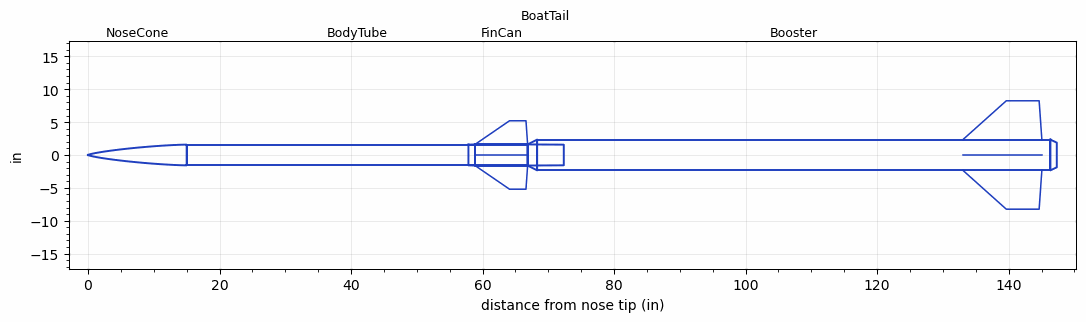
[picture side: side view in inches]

<RASAeroDocument>
 <FileVersion>2</FileVersion>
 <RocketDesign>
  <NoseCone>
   <Length>15</Length>
   <Diameter>3.15</Diameter>
   <Shape>Von Karman Ogive</Shape>
   <BluntRadius>0.1</BluntRadius>
   <Location>0</Location>
  </NoseCone>
  <BodyTube>
   <Length>51.85</Length>
   <Diameter>3.15</Diameter>
   <Location>15</Location>
  </BodyTube>
  <FinCan>
   <Length>8</Length>
   <Diameter>3.21</Diameter>
   <InsideDiameter>3.15</InsideDiameter>
   <Location>66.85</Location>
   <ShoulderLength>1</ShoulderLength>
   <Offset>-8</Offset>
   <Fin>
    <Count>4</Count>
    <Chord>8</Chord>
    <Span>3.6</Span>
    <SweepDistance>5.25</SweepDistance>
    <TipChord>2.5</TipChord>
    <Thickness>0.165</Thickness>
    <LERadius>0.015</LERadius>
    <Location>8</Location>
    <AirfoilSection>Hexagonal</AirfoilSection>
    <FX1>0.75</FX1>
    <FX3>0.75</FX3>
   </Fin>
  </FinCan>
  <BoatTail>
   <Length>5.5</Length>
   <Diameter>3.21</Diameter>
   <RearDiameter>3.14</RearDiameter>
   <Location>66.85</Location>
  </BoatTail>
  <Booster>
   <Length>78.05</Length>
   <Diameter>4.68</Diameter>
   <InsideDiameter>3.21</InsideDiameter>
   <RailGuideDiameter>0.5</RailGuideDiameter>
   <RailGuideHeight>0.5</RailGuideHeight>
   <Location>66.85</Location>
   <ShoulderLength>1.45</ShoulderLength>
   <BoattailLength>0.97</BoattailLength>
   <BoattailRearDiameter>3.75</BoattailRearDiameter>
   <Fin>
    <Count>4</Count>
    <Chord>12</Chord>
    <Span>5.9</Span>
    <SweepDistance>6.59</SweepDistance>
    <TipChord>5</TipChord>
    <Thickness>0.185</Thickness>
    <LERadius>0.02</LERadius>
    <Location>13.3</Location>
    <AirfoilSection>Hexagonal</AirfoilSection>
    <FX1>0.75</FX1>
    <FX3>0.75</FX3>
   </Fin>
  </Booster>
  <Surface>Smooth Paint</Surface>
  <ModifiedBarrowman>True</ModifiedBarrowman>
  <Turbulence>True</Turbulence>
  <SustainerNozzle>2.15</SustainerNozzle>
  <Booster1Nozzle>3.33</Booster1Nozzle>
  <UseBooster1>False</UseBooster1>
  <UseBooster2>False</UseBooster2>
 </RocketDesign>
 <LaunchSite>
  <Altitude>3910</Altitude>
  <Pressure>0</Pressure>
  <RodAngle>2.77</RodAngle>
  <RodLength>22</RodLength>
  <Temperature>65</Temperature>
  <WindSpeed>0</WindSpeed>
 </LaunchSite>
 <Recovery>
  <Altitude1>1000</Altitude1>
  <Altitude2>3000</Altitude2>
  <DeviceType1>Parachute</DeviceType1>
  <DeviceType2>Parachute</DeviceType2>
  <Event1>False</Event1>
  <Event2>False</Event2>
  <Size1>24</Size1>
  <Size2>36</Size2>
  <EventType1>Apogee</EventType1>
  <EventType2>Altitude</EventType2>
  <CD1>1.33</CD1>
  <CD2>1.33</CD2>
 </Recovery>
 <SimulationList>
  <Simulation>
   <SustainerEngine>M787  (KIP)</SustainerEngine>
   <SustainerLaunchWt>23.31</SustainerLaunchWt>
   <SustainerNozzleDiameter>2.15</SustainerNozzleDiameter>
   <SustainerCG>46</SustainerCG>
   <SustainerIgnitionDelay>15.16</SustainerIgnitionDelay>
   <Booster1Engine>O4374  (KIP)</Booster1Engine>
   <Booster1LaunchWt>87.05</Booster1LaunchWt>
   <Booster1SeparationDelay>0</Booster1SeparationDelay>
   <Booster1IgnitionDelay>0</Booster1IgnitionDelay>
   <Booster1CG>94.75</Booster1CG>
   <Booster1NozzleDiameter>3.33</Booster1NozzleDiameter>
   <IncludeBooster1>True</IncludeBooster1>
   <Booster2Delay>0</Booster2Delay>
   <IncludeBooster2>False</IncludeBooster2>
   <TimetoApogee>153.4794</TimetoApogee>
   <MaxAltitude>289789.3</MaxAltitude>
   <MaxVelocity>4094.815</MaxVelocity>
  </Simulation>
 </SimulationList>
</RASAeroDocument>
